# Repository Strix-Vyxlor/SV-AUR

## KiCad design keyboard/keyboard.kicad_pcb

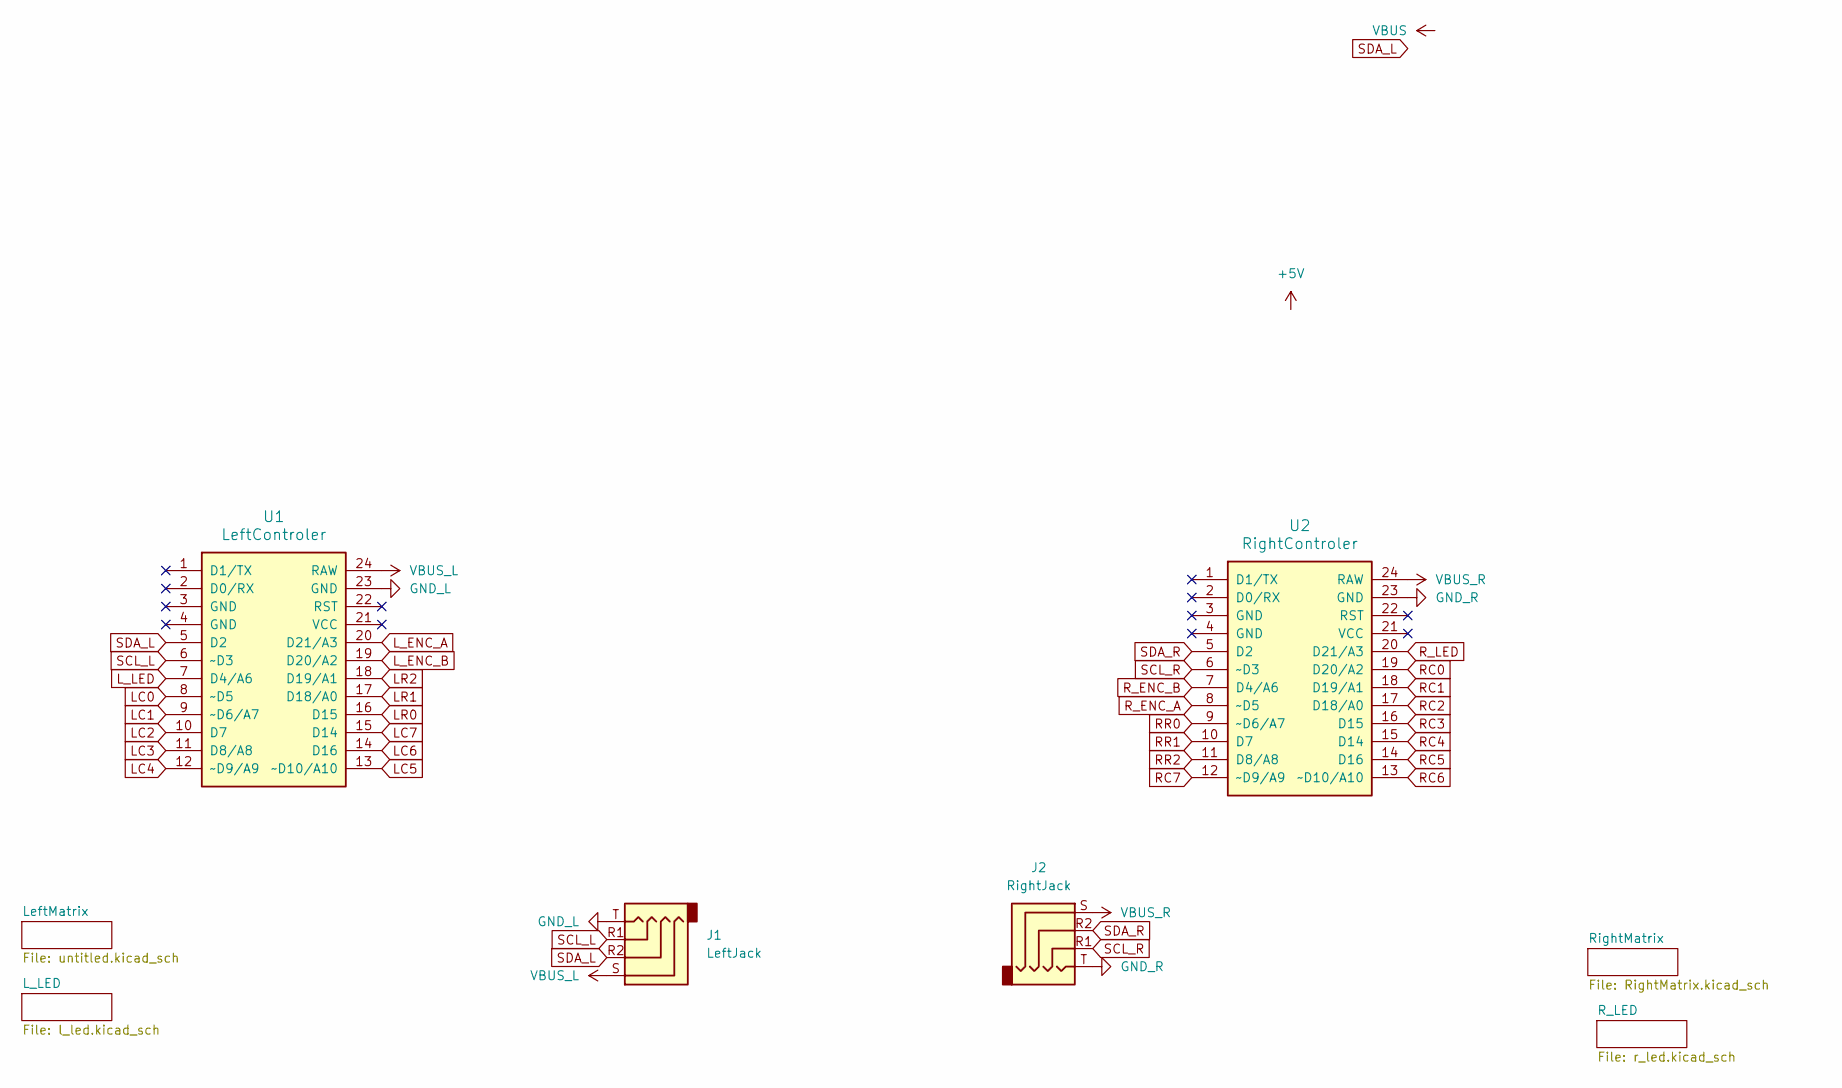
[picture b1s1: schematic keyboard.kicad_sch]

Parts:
J1: LeftJack; Jack_3.5mm_PJ320D_Horizontal
J2: RightJack; Jack_3.5mm_PJ320D_Horizontal
U1: LeftControler; Sparkfun_Pro_Micro
U2: RightControler; Sparkfun_Pro_Micro

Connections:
GND_L: J1.T, U1.23 (GND); also elsewhere on the board
GND_R: J2.T, U2.23 (GND); also elsewhere on the board
LC0: U1.8 (~D5); also elsewhere on the board
LC1: U1.9 (~D6/A7); also elsewhere on the board
LC2: U1.10 (D7); also elsewhere on the board
LC3: U1.11 (D8/A8); also elsewhere on the board
LC4: U1.12 (~D9/A9); also elsewhere on the board
LC5: U1.13 (~D10/A10); also elsewhere on the board
LC6: U1.14 (D16); also elsewhere on the board
LC7: U1.15 (D14); also elsewhere on the board
LR0: U1.16 (D15); also elsewhere on the board
LR1: U1.17 (D18/A0); also elsewhere on the board
LR2: U1.18 (D19/A1); also elsewhere on the board
L_ENC_A: U1.20 (D21/A3); also elsewhere on the board
L_ENC_B: U1.19 (D20/A2); also elsewhere on the board
L_LED: U1.7 (D4/A6); also elsewhere on the board
RC0: U2.19 (D20/A2); also elsewhere on the board
RC1: U2.18 (D19/A1); also elsewhere on the board
RC2: U2.17 (D18/A0); also elsewhere on the board
RC3: U2.16 (D15); also elsewhere on the board
RC4: U2.15 (D14); also elsewhere on the board
RC5: U2.14 (D16); also elsewhere on the board
RC6: U2.13 (~D10/A10); also elsewhere on the board
RC7: U2.12 (~D9/A9); also elsewhere on the board
RR0: U2.9 (~D6/A7); also elsewhere on the board
RR1: U2.10 (D7); also elsewhere on the board
RR2: U2.11 (D8/A8); also elsewhere on the board
R_ENC_A: U2.8 (~D5); also elsewhere on the board
R_ENC_B: U2.7 (D4/A6); also elsewhere on the board
R_LED: U2.20 (D21/A3); also elsewhere on the board
SCL_L: J1.R1, U1.6 (~D3)
SCL_R: J2.R1, U2.6 (~D3)
SDA_L: J1.R2, U1.5 (D2)
SDA_R: J2.R2, U2.5 (D2)
VBUS_L: J1.S, U1.24 (RAW); also elsewhere on the board
VBUS_R: J2.S, U2.24 (RAW); also elsewhere on the board

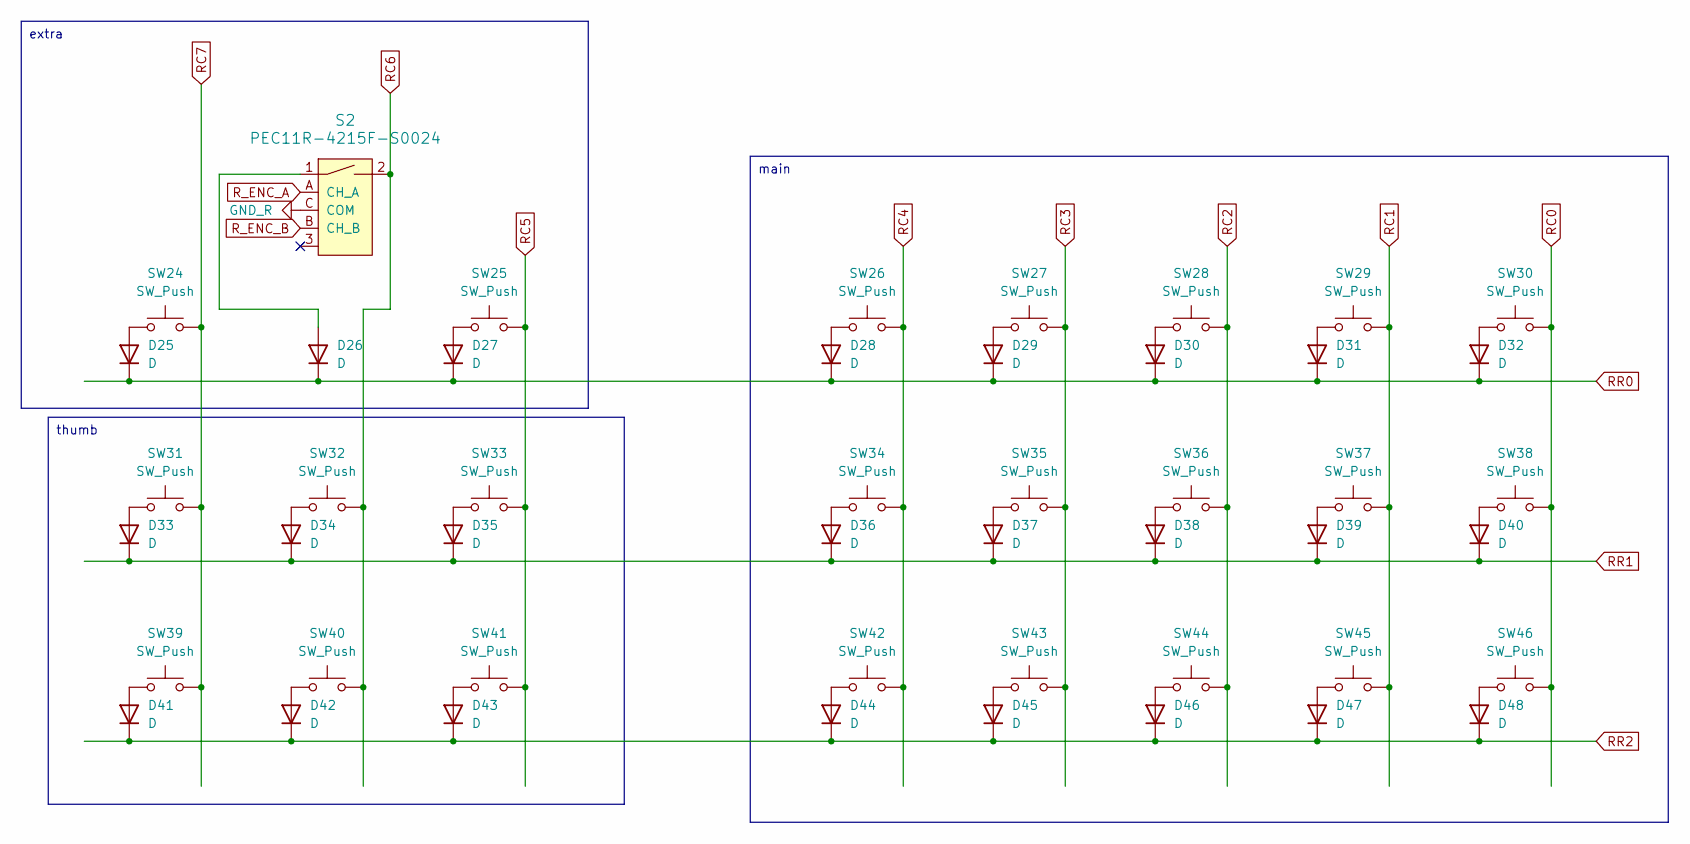
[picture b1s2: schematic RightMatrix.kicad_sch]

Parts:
D25, D26, D27, D28, D29, D30, D31, D32, D33, D34, D35, D36, D37, D38, D39, D40, D41, D42, D43, D44, D45, D46, D47, D48: D; D_SOD-123
S2: PEC11R-4215F-S0024; Rotary_Encoder_Switched_PEC11R; MPN PEC11R-4215F-S0024; Digi-Key_PN PEC11R-4215F-S0024-ND
SW24, SW25: SW_Push; SW_SPST_Omron_B3F-40xx
SW26, SW27, SW28, SW29, SW30, SW31, SW32, SW33, SW34, SW35, SW36, SW37, SW38, SW39, SW40, SW41, SW42, SW43, SW44, SW45, SW46: SW_Push; SW_Hotswap_Kailh_Choc_V1V2_1.00u

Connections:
GND_R: S2.C (COM); also elsewhere on the board
unnamed: D25.2 (A), SW24.1
unnamed: D26.2 (A), S2.1
unnamed: D27.2 (A), SW25.1
unnamed: D28.2 (A), SW26.1
unnamed: D29.2 (A), SW27.1
unnamed: D30.2 (A), SW28.1
unnamed: D31.2 (A), SW29.1
unnamed: D32.2 (A), SW30.1
unnamed: D33.2 (A), SW31.1
unnamed: D34.2 (A), SW32.1
unnamed: D35.2 (A), SW33.1
unnamed: D36.2 (A), SW34.1
unnamed: D37.2 (A), SW35.1
unnamed: D38.2 (A), SW36.1
unnamed: D39.2 (A), SW37.1
unnamed: D40.2 (A), SW38.1
unnamed: D41.2 (A), SW39.1
unnamed: D42.2 (A), SW40.1
unnamed: D43.2 (A), SW41.1
unnamed: D44.2 (A), SW42.1
unnamed: D45.2 (A), SW43.1
unnamed: D46.2 (A), SW44.1
unnamed: D47.2 (A), SW45.1
unnamed: D48.2 (A), SW46.1
RC0: SW30.2, SW38.2, SW46.2; also elsewhere on the board
RC1: SW29.2, SW37.2, SW45.2; also elsewhere on the board
RC2: SW28.2, SW36.2, SW44.2; also elsewhere on the board
RC3: SW27.2, SW35.2, SW43.2; also elsewhere on the board
RC4: SW26.2, SW34.2, SW42.2; also elsewhere on the board
RC5: SW25.2, SW33.2, SW41.2; also elsewhere on the board
RC6: S2.2, SW32.2, SW40.2; also elsewhere on the board
RC7: SW24.2, SW31.2, SW39.2; also elsewhere on the board
RR0: D25.1 (K), D26.1 (K), D27.1 (K), D28.1 (K), D29.1 (K), D30.1 (K), D31.1 (K), D32.1 (K); also elsewhere on the board
RR1: D33.1 (K), D34.1 (K), D35.1 (K), D36.1 (K), D37.1 (K), D38.1 (K), D39.1 (K), D40.1 (K); also elsewhere on the board
RR2: D41.1 (K), D42.1 (K), D43.1 (K), D44.1 (K), D45.1 (K), D46.1 (K), D47.1 (K), D48.1 (K); also elsewhere on the board
R_ENC_A: S2.A (CH_A); also elsewhere on the board
R_ENC_B: S2.B (CH_B); also elsewhere on the board

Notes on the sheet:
extra
main
thumb

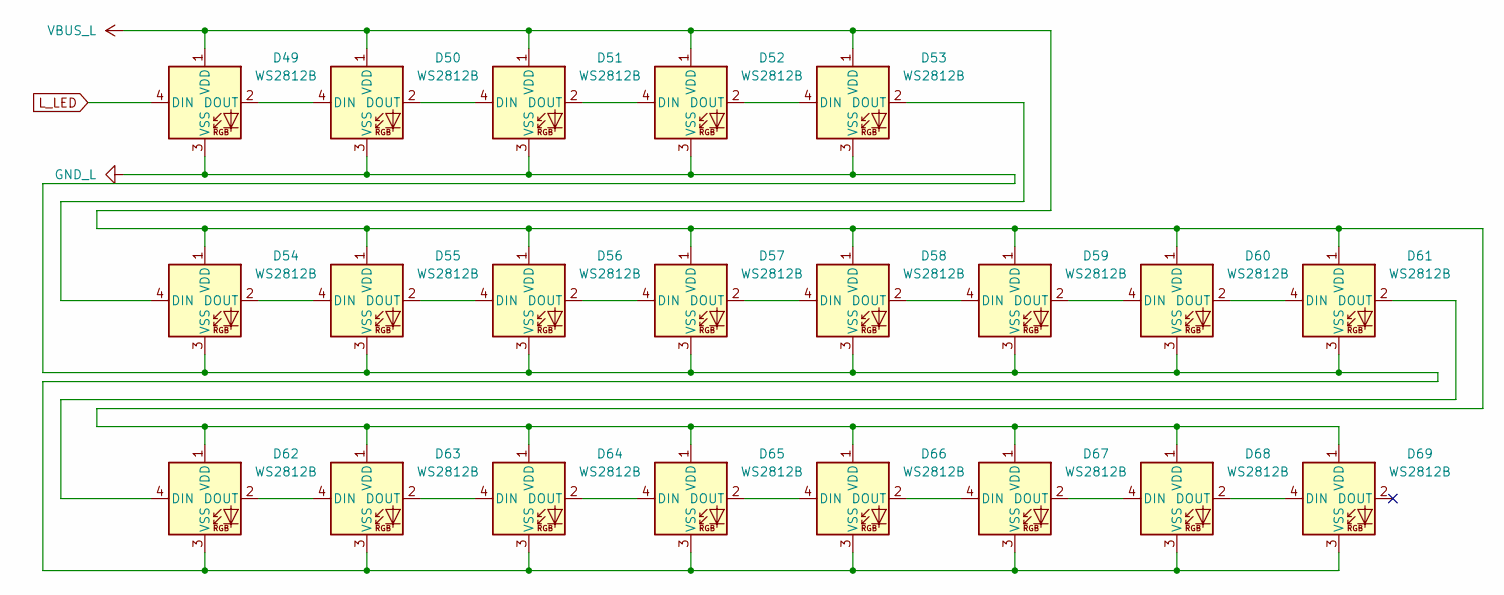
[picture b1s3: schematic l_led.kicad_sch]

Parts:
D49, D50, D51, D52, D53, D54, D55, D56, D57, D58, D59, D60, D61, D62, D63, D64, D65, D66, D67, D68, D69: WS2812B; MX_SK6812MINI-E

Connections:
GND_L: D49.3 (VSS), D50.3 (VSS), D51.3 (VSS), D52.3 (VSS), D53.3 (VSS), D54.3 (VSS), D55.3 (VSS), D56.3 (VSS), D57.3 (VSS), D58.3 (VSS), D59.3 (VSS), D60.3 (VSS), D61.3 (VSS), D62.3 (VSS), D63.3 (VSS), D64.3 (VSS), D65.3 (VSS), D66.3 (VSS), D67.3 (VSS), D68.3 (VSS), D69.3 (VSS); also elsewhere on the board
L_LED: D49.4 (DIN); also elsewhere on the board
unnamed: D49.2 (DOUT), D50.4 (DIN)
unnamed: D50.2 (DOUT), D51.4 (DIN)
unnamed: D51.2 (DOUT), D52.4 (DIN)
unnamed: D52.2 (DOUT), D53.4 (DIN)
unnamed: D53.2 (DOUT), D54.4 (DIN)
unnamed: D54.2 (DOUT), D55.4 (DIN)
unnamed: D55.2 (DOUT), D56.4 (DIN)
unnamed: D56.2 (DOUT), D57.4 (DIN)
unnamed: D57.2 (DOUT), D58.4 (DIN)
unnamed: D58.2 (DOUT), D59.4 (DIN)
unnamed: D59.2 (DOUT), D60.4 (DIN)
unnamed: D60.2 (DOUT), D61.4 (DIN)
unnamed: D61.2 (DOUT), D62.4 (DIN)
unnamed: D62.2 (DOUT), D63.4 (DIN)
unnamed: D63.2 (DOUT), D64.4 (DIN)
unnamed: D64.2 (DOUT), D65.4 (DIN)
unnamed: D65.2 (DOUT), D66.4 (DIN)
unnamed: D66.2 (DOUT), D67.4 (DIN)
unnamed: D67.2 (DOUT), D68.4 (DIN)
unnamed: D68.2 (DOUT), D69.4 (DIN)
VBUS_L: D49.1 (VDD), D50.1 (VDD), D51.1 (VDD), D52.1 (VDD), D53.1 (VDD), D54.1 (VDD), D55.1 (VDD), D56.1 (VDD), D57.1 (VDD), D58.1 (VDD), D59.1 (VDD), D60.1 (VDD), D61.1 (VDD), D62.1 (VDD), D63.1 (VDD), D64.1 (VDD), D65.1 (VDD), D66.1 (VDD), D67.1 (VDD), D68.1 (VDD), D69.1 (VDD); also elsewhere on the board

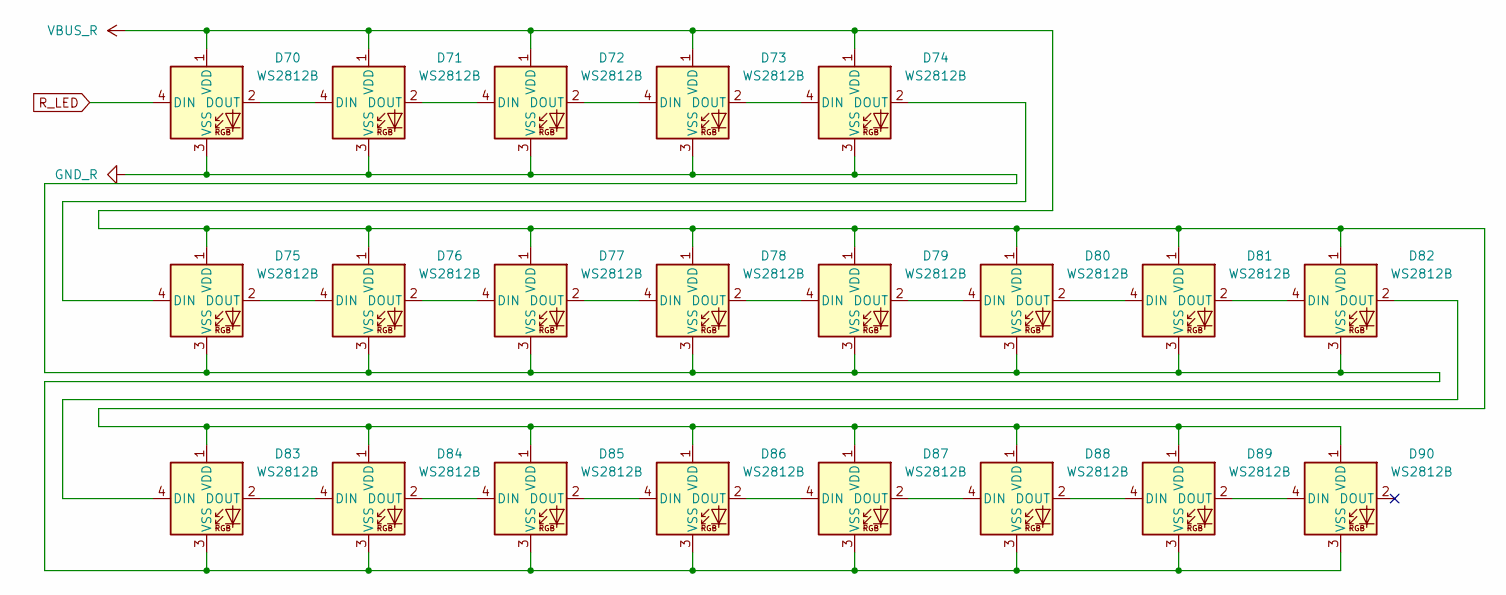
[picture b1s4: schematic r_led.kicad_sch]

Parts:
D70, D71, D72, D73, D74, D75, D76, D77, D78, D79, D80, D81, D82, D83, D84, D85, D86, D87, D88, D89, D90: WS2812B; MX_SK6812MINI-E

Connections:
GND_R: D70.3 (VSS), D71.3 (VSS), D72.3 (VSS), D73.3 (VSS), D74.3 (VSS), D75.3 (VSS), D76.3 (VSS), D77.3 (VSS), D78.3 (VSS), D79.3 (VSS), D80.3 (VSS), D81.3 (VSS), D82.3 (VSS), D83.3 (VSS), D84.3 (VSS), D85.3 (VSS), D86.3 (VSS), D87.3 (VSS), D88.3 (VSS), D89.3 (VSS), D90.3 (VSS); also elsewhere on the board
unnamed: D70.2 (DOUT), D71.4 (DIN)
unnamed: D71.2 (DOUT), D72.4 (DIN)
unnamed: D72.2 (DOUT), D73.4 (DIN)
unnamed: D73.2 (DOUT), D74.4 (DIN)
unnamed: D74.2 (DOUT), D75.4 (DIN)
unnamed: D75.2 (DOUT), D76.4 (DIN)
unnamed: D76.2 (DOUT), D77.4 (DIN)
unnamed: D77.2 (DOUT), D78.4 (DIN)
unnamed: D78.2 (DOUT), D79.4 (DIN)
unnamed: D79.2 (DOUT), D80.4 (DIN)
unnamed: D80.2 (DOUT), D81.4 (DIN)
unnamed: D81.2 (DOUT), D82.4 (DIN)
unnamed: D82.2 (DOUT), D83.4 (DIN)
unnamed: D83.2 (DOUT), D84.4 (DIN)
unnamed: D84.2 (DOUT), D85.4 (DIN)
unnamed: D85.2 (DOUT), D86.4 (DIN)
unnamed: D86.2 (DOUT), D87.4 (DIN)
unnamed: D87.2 (DOUT), D88.4 (DIN)
unnamed: D88.2 (DOUT), D89.4 (DIN)
unnamed: D89.2 (DOUT), D90.4 (DIN)
R_LED: D70.4 (DIN); also elsewhere on the board
VBUS_R: D70.1 (VDD), D71.1 (VDD), D72.1 (VDD), D73.1 (VDD), D74.1 (VDD), D75.1 (VDD), D76.1 (VDD), D77.1 (VDD), D78.1 (VDD), D79.1 (VDD), D80.1 (VDD), D81.1 (VDD), D82.1 (VDD), D83.1 (VDD), D84.1 (VDD), D85.1 (VDD), D86.1 (VDD), D87.1 (VDD), D88.1 (VDD), D89.1 (VDD), D90.1 (VDD); also elsewhere on the board

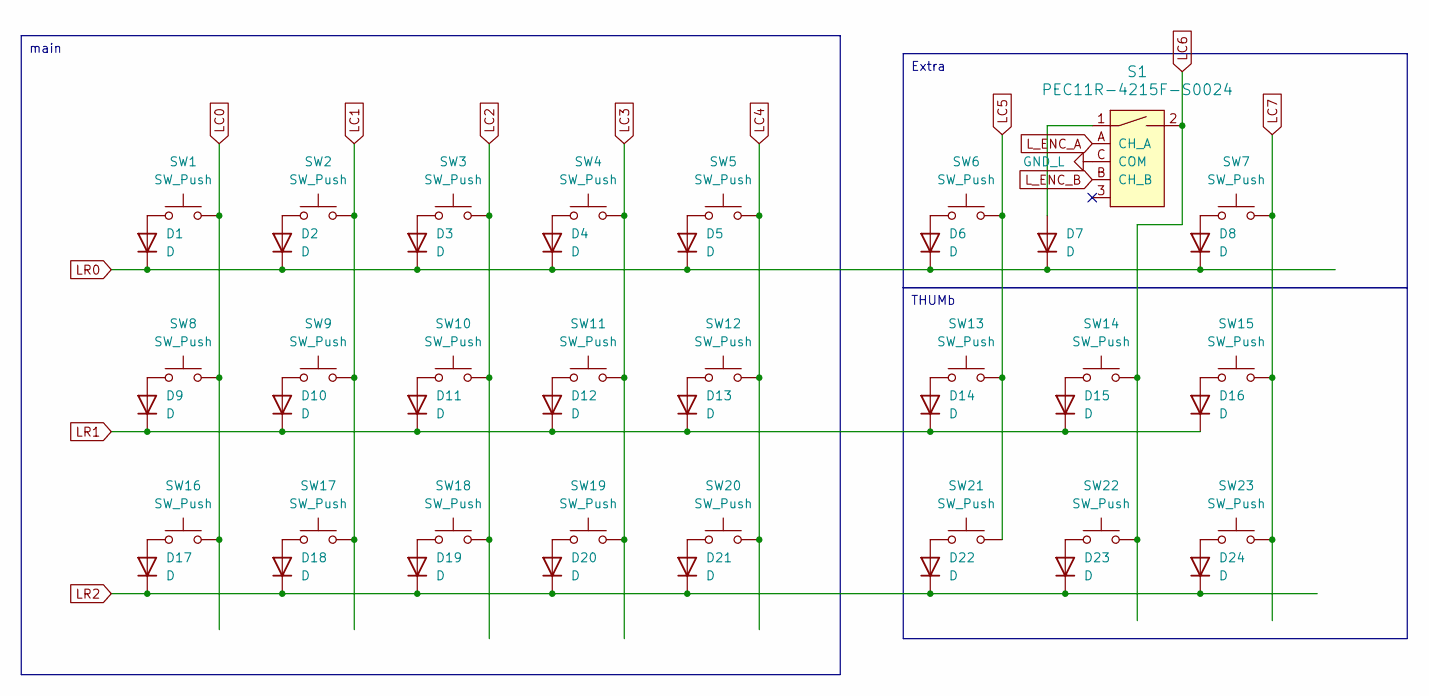
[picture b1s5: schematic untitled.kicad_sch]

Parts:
D1, D2, D3, D4, D5, D6, D7, D8, D9, D10, D11, D12, D13, D14, D15, D16, D17, D18, D19, D20, D21, D22, D23, D24: D; D_SOD-123
S1: PEC11R-4215F-S0024; Rotary_Encoder_Switched_PEC11R; MPN PEC11R-4215F-S0024; Digi-Key_PN PEC11R-4215F-S0024-ND
SW1, SW2, SW3, SW4, SW5, SW8, SW9, SW10, SW11, SW12, SW13, SW14, SW15, SW16, SW17, SW18, SW19, SW20, SW21, SW22, SW23: SW_Push; SW_Hotswap_Kailh_Choc_V1V2_1.00u
SW6, SW7: SW_Push; SW_SPST_Omron_B3F-40xx

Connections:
GND_L: S1.C (COM); also elsewhere on the board
LC0: SW1.2, SW8.2, SW16.2; also elsewhere on the board
LC1: SW2.2, SW9.2, SW17.2; also elsewhere on the board
LC2: SW3.2, SW10.2, SW18.2; also elsewhere on the board
LC3: SW4.2, SW11.2, SW19.2; also elsewhere on the board
LC4: SW5.2, SW12.2, SW20.2; also elsewhere on the board
LC5: SW6.2, SW13.2, SW21.2; also elsewhere on the board
LC6: S1.2, SW14.2, SW22.2; also elsewhere on the board
LC7: SW7.2, SW15.2, SW23.2; also elsewhere on the board
LR0: D1.1 (K), D2.1 (K), D3.1 (K), D4.1 (K), D5.1 (K), D6.1 (K), D7.1 (K), D8.1 (K); also elsewhere on the board
LR1: D9.1 (K), D10.1 (K), D11.1 (K), D12.1 (K), D13.1 (K), D14.1 (K), D15.1 (K), D16.1 (K); also elsewhere on the board
LR2: D17.1 (K), D18.1 (K), D19.1 (K), D20.1 (K), D21.1 (K), D22.1 (K), D23.1 (K), D24.1 (K); also elsewhere on the board
L_ENC_A: S1.A (CH_A); also elsewhere on the board
L_ENC_B: S1.B (CH_B); also elsewhere on the board
unnamed: D1.2 (A), SW1.1
unnamed: D2.2 (A), SW2.1
unnamed: D3.2 (A), SW3.1
unnamed: D4.2 (A), SW4.1
unnamed: D5.2 (A), SW5.1
unnamed: D6.2 (A), SW6.1
unnamed: D7.2 (A), S1.1
unnamed: D8.2 (A), SW7.1
unnamed: D9.2 (A), SW8.1
unnamed: D10.2 (A), SW9.1
unnamed: D11.2 (A), SW10.1
unnamed: D12.2 (A), SW11.1
unnamed: D13.2 (A), SW12.1
unnamed: D14.2 (A), SW13.1
unnamed: D15.2 (A), SW14.1
unnamed: D16.2 (A), SW15.1
unnamed: D17.2 (A), SW16.1
unnamed: D18.2 (A), SW17.1
unnamed: D19.2 (A), SW18.1
unnamed: D20.2 (A), SW19.1
unnamed: D21.2 (A), SW20.1
unnamed: D22.2 (A), SW21.1
unnamed: D23.2 (A), SW22.1
unnamed: D24.2 (A), SW23.1

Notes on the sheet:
THUMb
main
Extra

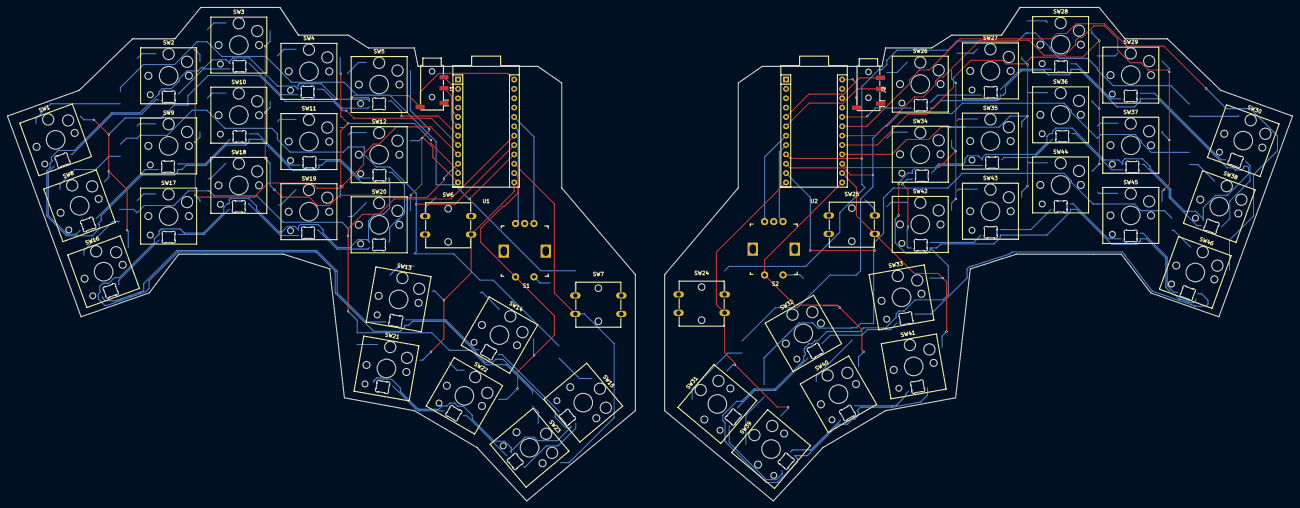
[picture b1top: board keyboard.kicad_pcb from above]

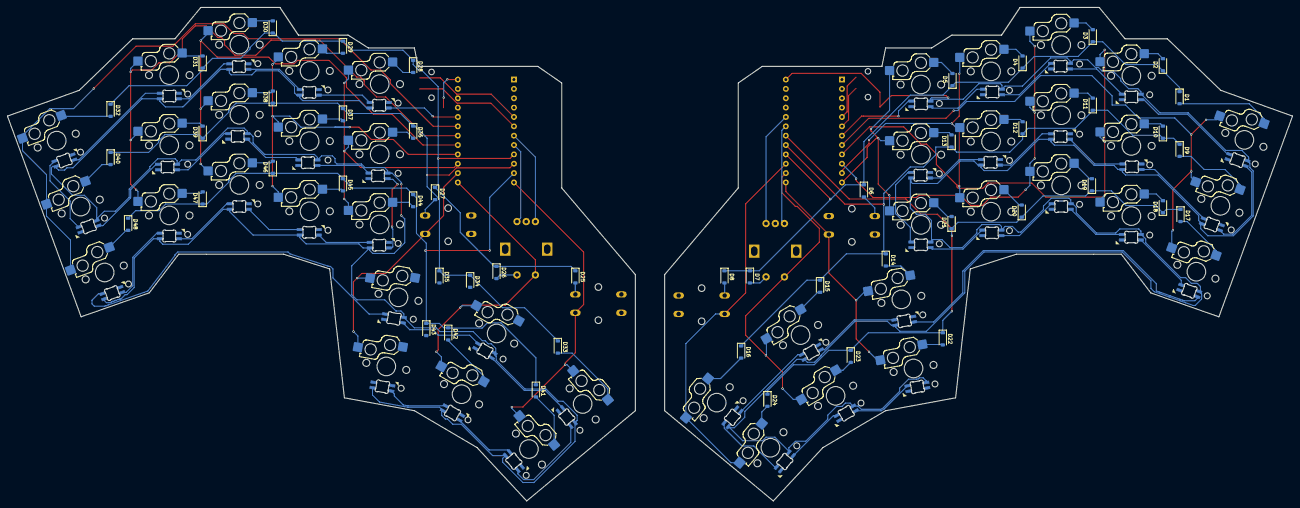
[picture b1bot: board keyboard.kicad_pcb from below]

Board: 2 copper layers, 348.9 x 134.0 mm, 142 parts (48 on the bottom side), 124 nets.

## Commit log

2024-06-20 initial-commit
